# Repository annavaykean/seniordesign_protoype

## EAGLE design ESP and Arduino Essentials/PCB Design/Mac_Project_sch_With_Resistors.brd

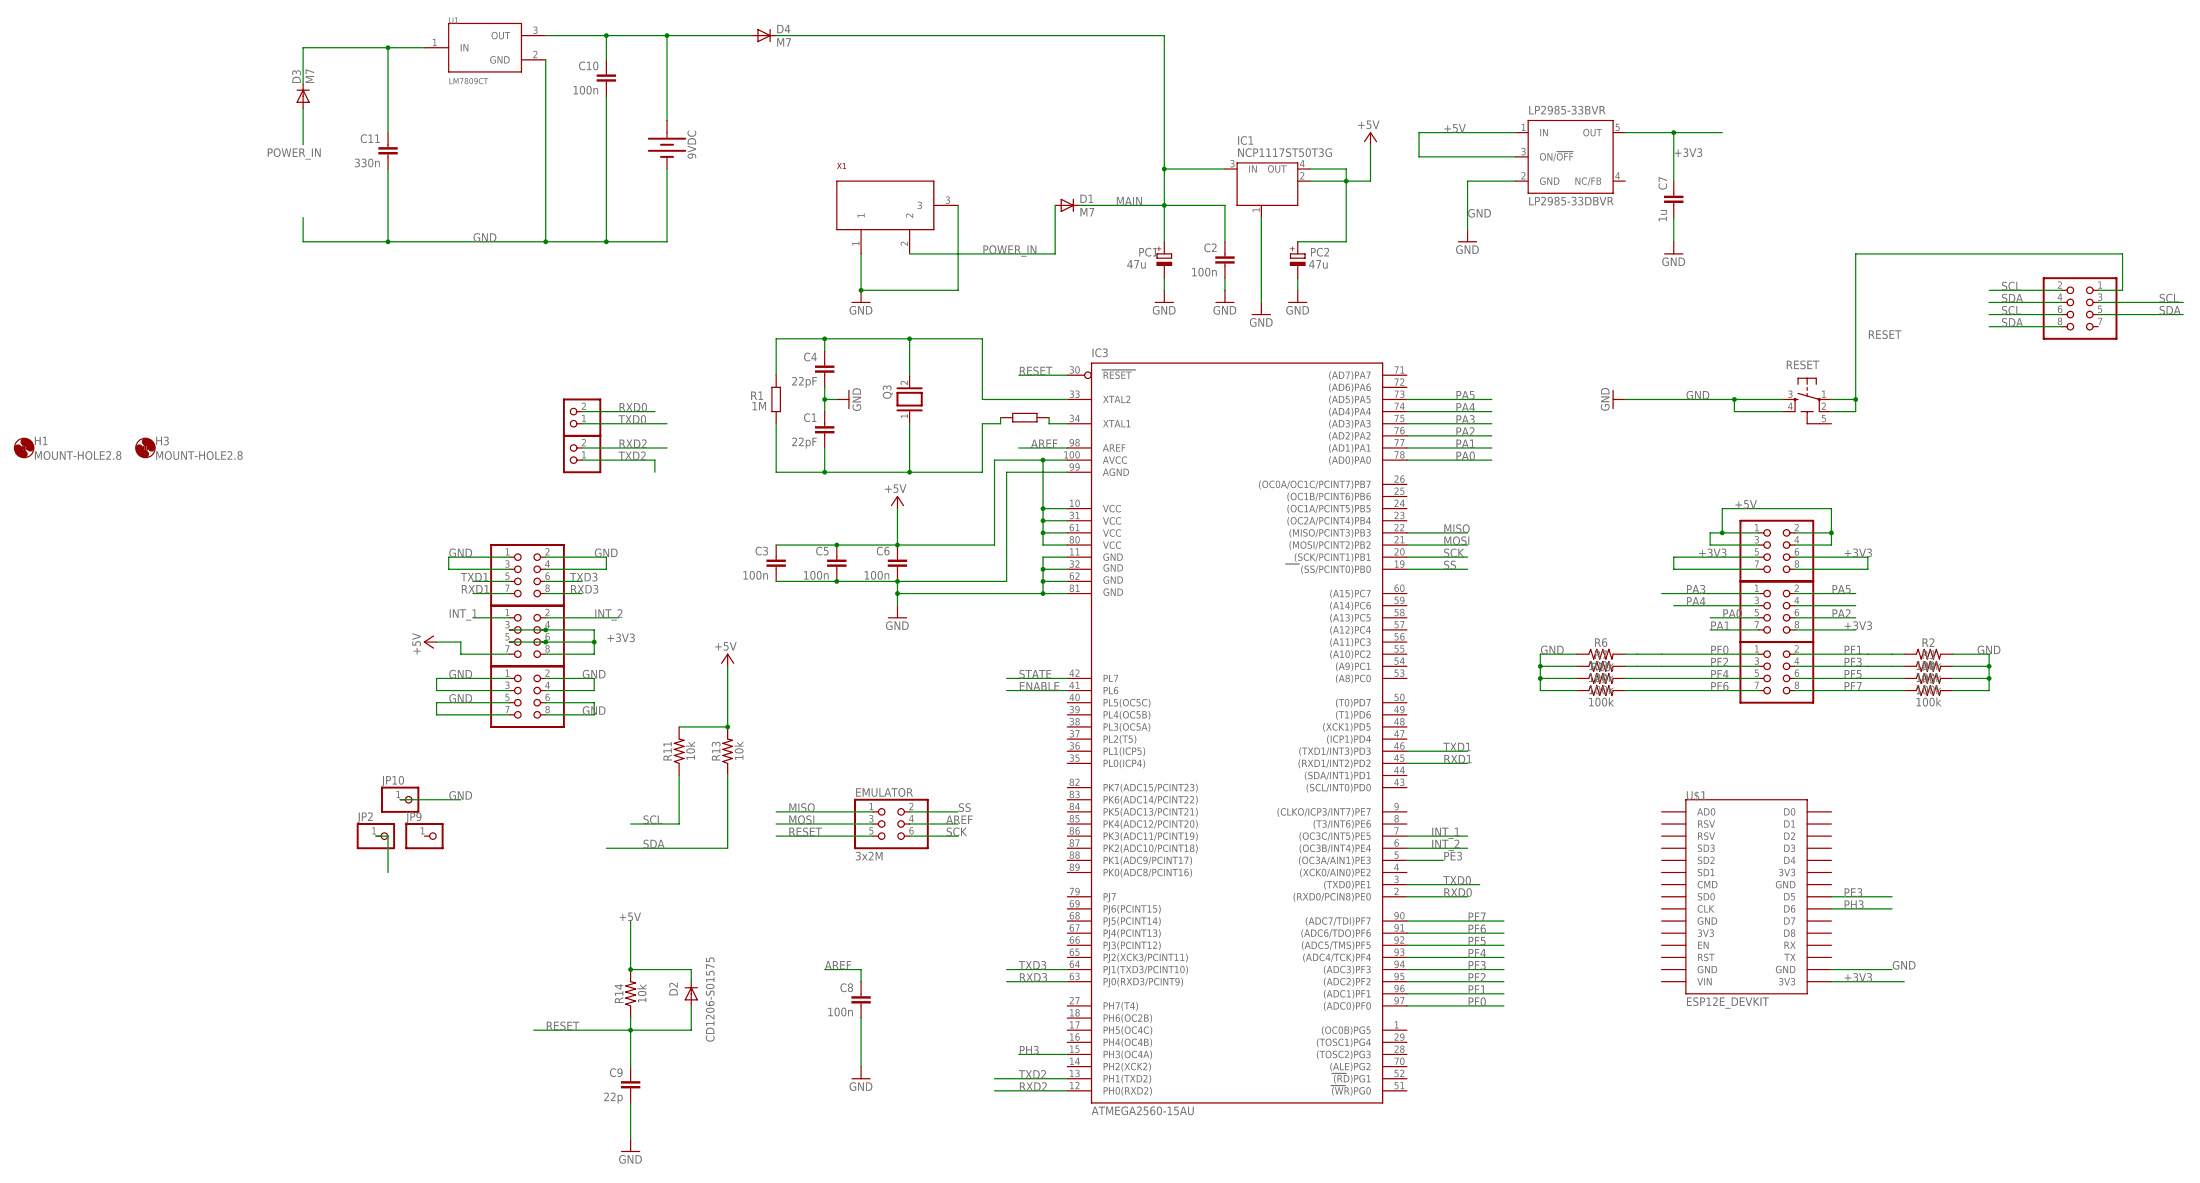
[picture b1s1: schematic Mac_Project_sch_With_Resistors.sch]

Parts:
1X1, 1X2: 1x2; 1X02
9VDC: BATTERY-9V; BATTCON_9V
C1, C4: 22pF; C0603-ROUND
C2, C3, C5, C6, C8, C10: 100n; C0603-ROUND
C7: 1u; C0603-ROUND
C9: 22p; C0603-ROUND
C11: 330n; C0603-ROUND
D1, D3, D4: M7; SMB
D2: CD1206-S01575; MINIMELF
EMULATOR: 3x2M; 2X03
H1, H3: MOUNT-HOLE2.8; 2,8
IC1: NCP1117ST50T3G; SOT223
IC3: ATMEGA2560-15AU; TQFP100
JP1, JP3, JP4, JP5, JP6, JP7, JP8: PINHD-2X4; 2X04
JP2, JP9, JP10: PINHD-1X1; 1X01
LP2985-33BVR: LP2985-33DBVR; SOT23-DBV
PC1, PC2: 47u; PANASONIC_D
Q3: 16MHz; QS
R1: 1M; R0603-ROUND
R2, R3, R4, R5, R6, R7, R9, R10: 100k; 0603
R11, R13, R14: 10k; 0603
R12: 27O; R0603-ROUND
RESET: TS42
U1: LM7809CT; TO254P470X1016X1879-3P
U$1: ESP12E_DEVKIT
X1: POWERSUPPLY_DC21MMX; POWERSUPPLY_DC-21MM

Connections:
5-GND: RESET.5 (5-GND)
+3V3: C7.2, JP3.5, JP3.6, JP3.7, JP3.8, JP4.8, JP7.3, JP7.4, JP7.5, JP7.6, JP7.8, LP2985-33BVR.5 (OUT), U$1.3V3@2 (3V3)
+5V: C3.1, C5.1, C6.1, D2.C, IC1.2 (OUT), IC1.4 (OUT), IC3.10 (VCC), IC3.31 (VCC1), IC3.61 (VCC2), IC3.80 (VCC3), IC3.100 (AVCC), JP3.1, JP3.2, JP3.3, JP3.4, JP7.7, LP2985-33BVR.1 (IN), LP2985-33BVR.3 (ON/!OFF), PC2.+, R11.2, R13.2, R14.2
AREF: C8.1, EMULATOR.4, IC3.98 (AREF)
ENABLE: IC3.41 (PL6)
GND: 9VDC.-, C1.1, C2.2, C3.2, C4.2, C5.2, C6.2, C7.1, C8.2, C9.2, C10.2, C11.2, IC1.1 (GND/ADJ), IC3.11 (GND), IC3.32 (GND1), IC3.62 (GND2), IC3.81 (GND3), IC3.99 (AGND), JP1.1, JP1.2, JP1.3, JP1.4, JP1.5, JP1.6, JP1.7, JP1.8, JP4.4, JP6.1, JP6.2, JP6.3, JP6.4, JP10.1, LP2985-33BVR.2 (GND), PC1.-, PC2.-, R2.2, R3.2, R4.2, R5.2, R6.1, R7.1, R9.1, R10.1, RESET.3, RESET.4, U1.2 (GND), U$1.GND@3 (GND), X1.1, X1.3
INT_1: IC3.7 ((OC3C/INT5)PE5), JP7.1
INT_2: IC3.6 ((OC3B/INT4)PE4), JP7.2
MAIN: C2.1, D1.C, D4.C, IC1.3 (IN), PC1.+
MISO: EMULATOR.1, IC3.22 ((MISO/PCINT3)PB3)
MOSI: EMULATOR.3, IC3.21 ((MOSI/PCINT2)PB2)
unnamed: C4.1, IC3.33 (XTAL2), Q3.2, R1.2
unnamed: C1.2, Q3.1, R1.1, R12.1
unnamed: IC3.34 (XTAL1), R12.2
unnamed: C11.1, D3.C, U1.1 (IN)
unnamed: 9VDC.+, C10.1, D4.A, U1.3 (OUT)
PA0: IC3.78 ((AD0)PA0), JP4.5
PA1: IC3.77 ((AD1)PA1), JP4.7
PA2: IC3.76 ((AD2)PA2), JP4.6
PA3: IC3.75 ((AD3)PA3), JP4.1
PA4: IC3.74 ((AD4)PA4), JP4.3
PA5: IC3.73 ((AD5)PA5), JP4.2
PE3: IC3.5 ((OC3A/AIN1)PE3), U$1.D5
PF0: IC3.97 ((ADC0)PF0), JP8.1, R6.2
PF1: IC3.96 ((ADC1)PF1), JP8.2, R2.1
PF2: IC3.95 ((ADC2)PF2), JP8.3, R7.2
PF3: IC3.94 ((ADC3)PF3), JP8.4, R3.1
PF4: IC3.93 ((ADC4/TCK)PF4), JP8.5, R10.2
PF5: IC3.92 ((ADC5/TMS)PF5), JP8.6, R4.1
PF6: IC3.91 ((ADC6/TDO)PF6), JP8.7, R9.2
PF7: IC3.90 ((ADC7/TDI)PF7), JP8.8, R5.1
PH3: IC3.15 (PH3(OC4A)), U$1.D6
POWER_IN: D1.A, D3.A, X1.2
RESET: C9.1, D2.A, EMULATOR.5, IC3.30 (RESET), JP5.1, R14.1, RESET.1, RESET.2
RXD0: 1X2.2, IC3.2 ((RXD0/PCIN8)PE0)
RXD1: IC3.45 ((RXD1/INT2)PD2), JP6.7
RXD2: 1X1.2, IC3.12 (PH0(RXD2))
RXD3: IC3.63 (PJ0(RXD3/PCINT9)), JP6.8
SCK: EMULATOR.6, IC3.20 ((SCK/PCINT1)PB1)
SCL: JP5.2, JP5.3, JP5.6, R11.1
SDA: JP5.4, JP5.5, JP5.8, R13.1
SS: EMULATOR.2, IC3.19 ((SS/PCINT0)PB0)
STATE: IC3.42 (PL7)
TXD0: 1X2.1, IC3.3 ((TXD0)PE1)
TXD1: IC3.46 ((TXD1/INT3)PD3), JP6.5
TXD2: 1X1.1, IC3.13 (PH1(TXD2))
TXD3: IC3.64 (PJ1(TXD3/PCINT10)), JP6.6

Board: 2 copper layers, 54 parts (0 on the bottom side), 44 nets, no tracks yet.

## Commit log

2019-04-02 initial commit with DB script
2019-04-04 project exists now
2019-04-11 initial flutter project
2019-04-11 100 page doc
2019-04-11 added A's section and fixed A's works cited
2019-04-11 Update 100 page.docx
    my stuff is there and still organizing some
2019-04-11 Moved Schematic to new section
    moved schematic, added description
2019-04-11 Update 100 page.docx
    Heading fixed
2019-04-11 Update 100 page.docx
    partial format fix
2019-04-11 Update 100 page.docx
    go ahead
2019-04-11 Additions and formatting
    added a page from myself and 3.5 pages from mack, reformatted numbering in ch. 4 & 5. TOC taking very long to update
2019-04-12 Update 100 page.docx
    done with my part
2019-04-12 10 pages finished, page count issue
    page counter was incorrect, we are short 8 pages, 6 short from mac. formatting will give us 1/2 page on correcting titel size and spacing.
2019-04-12 added more from mack
    seperately writing more to try and fill mack's gap. go ahead with indexing
2019-04-12 added more texgt and inline citations.
    most of my citations are general so I placed them at the end of the paragraph/section
2019-04-12 citations indexed
2019-04-12 added two pages . we need 1.5
    github is giving me an error in regards to the excel file.
2019-04-12 New
    New document but the same
2019-04-12 renamed file
2019-04-12 fixed stuff
2019-04-12 hit page count
2019-04-13 Updated all headings
    fixed font inconsistencies in headings.
2019-04-18 Create Final Document Research .docx
    new document
2019-04-18 my part is added
2019-04-19 Update Final Document Research .docx
    more from my part
2019-04-19 adding my 5 pgs
2019-04-20 Added pages & labeled tables
    added pages. labeled all tables and figures
2019-04-20 Final doc Research updated
    moved changes over to correct doc
2019-04-20 Update Final Document Research .docx
    updated more bluetooth
2019-04-20 Update Final Document Research .docx
    editing format
2019-04-20 Updates
    Added page. 114 pages, 123 total. need 6. still awaiting 5 from mack
2019-04-20 hit page count
    Added mack's pages.
2019-04-20 Update Final Document Research .docx
    Bluetooth Low Energy
2019-04-20 Update Final Document Research .docx
    more BLE stuff
2019-04-20 Works Cited Fix #1
2019-04-20 works cited to IEEE format Pt.1
2019-04-20 added works cited to main paper
    use the works cited within the body of the paper now!
2019-04-21 Citations Update
    -Added citations to sections missing, moved inline
    -removed 5.1.2.1.2 & 2.2
2019-04-21 added more of Annavay's writing in
2019-04-21 Update Final Document Research .docx
    fixed minor format
2019-04-21 Update fixedWorksCited.docx
    more links
2019-04-21 Update fixedWorksCited.docx
    updated links
2019-04-21 Table updates
    -renumbered tables
2019-04-21 fixed works cited
2019-04-21 Add files via upload
    format fix
2019-04-21 format fixes
2019-04-22 Tables relabeled
    Relabeled tables, adjusted white spaces & orphan headings
    Preliminary proof reading
2019-04-22 Update to 120Final
    -formatting fixes
2019-04-22 updated final and created binded
    binded doc needs review
2019-04-22 small fix
2019-04-22 spacing fix
2019-04-22 undo change
2019-05-08 Super basic page navigation and working on Firebase
2019-05-09 foundation for bluetooth connections
2019-05-13 can scan for bluetooth device, working on display
2019-05-13 kinda displays scanned devices...but causes visual overflow
2019-05-13 prints list of bluetooth devices nearby
2019-05-13 kind of connecting to device
2019-05-14 Thien test this one!
2019-05-15 Update bluetooth_test_screen.dart
    seconds
2019-05-17 uploading notes from first lecture
2019-05-17 notes
2019-05-17 screen to test sending data over bluetooth
2019-05-17 alignment and global connection object for bluetooth
2019-05-19 Important Libaries and Instructions
2019-05-20 updated guides
2019-05-20 with tested code
2019-05-20 bluetooth improvements: display device name & read characteristics
2019-05-20 with code
2019-05-21 fixed bug: duplicate device listings on scan
2019-05-22 kinda-sorta reading characteristics
2019-05-22 minor change for safe testing
2019-05-22 testing the errors
2019-05-23 basic sign in added
2019-05-23 account creation added
2019-05-24 go to dashboard after sign in/up
2019-05-27 changes to alignment
2019-05-27 form validation for sign in
2019-05-27 can write data to database
2019-05-28 Bluetooth Receive Data
2019-05-29 read from firebase database
2019-05-29 bluetooth - sendInt update; database - organize fetched data
2019-05-29 close connection on logout
2019-05-31 more ESP32
2019-05-31 library
2019-05-31 read firebase data and display on UI
2019-05-31 CDR added
2019-05-31 can see database pull
2019-06-03 move folders
2019-06-03 begin work on chart, UI improvements
2019-06-14 added scatter plot
2019-06-16 charts work, adding images
2019-06-18 can recommend pose
    poses recommendations are randomly generated at the moment
    in future will use posture data to tailor recommendations
2019-06-18 added more poses
2019-06-19 more poses; settings screen has toggles
2019-06-20 settings menu alters flags in firebase
2019-06-21 addressed sign out bug
2019-06-21 basic notification working
2019-06-21 notification with noise and vibration
2019-06-21 pin get/set via user preferences
2019-06-24 default data to hold chart shape; trim email to prevent error
2019-06-24 swipe left for settings
2019-06-24 fixed issue of user preferences on sign up
2019-06-25 added long term data
2019-06-27 check if email or pin already used on sign up
2019-06-27 pin verification visuals updated
2019-06-28 phone notification based on firebase flag
2019-06-28 long term data anchor points are now white
2019-07-01 bug fixes
2019-07-02 code 4 demo
2019-07-02 upload
2019-07-02 working serial
2019-07-02 Major bug fix
    cogxy code
2019-07-03 can send pos/neg values
2019-07-03 can receive negative values
2019-07-04 Cogx Cogy sending code
    properly sending cog x & cog y, both negative and positive values. currently under leaning fwd condition
2019-07-04 Sensor to Firebase
    we established the proper serial communication, along along with sending to firebase
2019-07-05 fixed pin bug on sign up
2019-07-05 Create flipped cogxy test.ino
    code for testing flipped x y on recieve and breaking after multiple iterations
2019-07-05 Create cogxcogy_all_conditions.ino
    working transmit for all leaning conditions
2019-07-05 Update cogxcogy_all_conditions.ino
    added additional character to transmit string
2019-07-05 Force Sensor
    the 4 other position is functional
2019-07-05 Update cogxcogy_all_conditions2.ino
    added code to test vibrate modules using leds- good for left & right conditions
2019-07-08 fix signup + new timer (getUp reminder)
2019-07-08 Thien, let's try this
2019-07-09 Create cogxcogy_all_conditions3.ino
    working code for cog x and y no led notifications
2019-07-09 Update cogxcogy_all_conditions3.ino
    added 0 condition
2019-07-09 delay improved garbled data
2019-07-09 working with less errors
2019-07-09 timer code for rudy
2019-07-09 CODE WORKS
    The delay is at 10 seconds and did not give error codes
2019-07-09 fixed chart data load bug
2019-07-09 TURN ON LED/VIBRATOR
2019-07-10 Create cogxcogy_all_conditions4.ino
    added led code to simulate vibrate module. recieves on off trigger
2019-07-10 Create vibtest.ino
    code to run single vibrate module
2019-07-10 Change Firebase Directory to Annavay
2019-07-10 Vibrator Module Included
2019-07-10 Update cogxcogy_all_conditions4.ino
    working vibrate module toggle with bad posture condition.
2019-07-11 Update VIBRATOR_Arduino.ino
    code that sends sensor data to wifi module then to firebase
2019-07-11 My Integrated Code
    some of the code works, so some are just partial
2019-07-12 Full Integration
    Sensor and Vibrator code works and sends to firebase
2019-07-12 Update cogxcogy_all_conditions4.ino
    working code. use file labeled arduino works rev1
2019-07-12 working FSR code & Full duplex code
    FSR fully working in test code
    rev1 is working full duplex. baud cannot exceed 57600 for s.begin
2019-07-12 Clean Code
    Comments and White space are cleaned out on the code
2019-07-12 Update Arduino_works_completely_rev1.ino
    full duplex works correctly
2019-07-12 WiFi Optimized
    wifi does not crash on data read and transmit
2019-07-12 fixing cache issue
2019-07-12 User got up
2019-07-12 Optimize Code
2019-07-14 Update Arduino_works_completely_rev1.ino
    changes to tx3/rx3 works on pcb
2019-07-15 Create Arduino_works_completely_rev2.ino
    updated to include additional sensors and new serial comm pins for pcb
2019-07-15 updated stretch page, added conference paper
2019-07-16 increased anchors on charts
2019-07-16 added intro and overview to conference paper
2019-07-17 rev 3 created
    sensors in final position, cog x & y not updated yet
2019-07-17 Update Arduino_works_completely_rev3.ino
    small test changes
2019-07-17 got 4 pages
2019-07-18 almost 5 pages
2019-07-18 added mack's portion
2019-07-18 proof me
2019-07-18 Organizing format
    Updated biography and formatting
2019-07-18 added A's pic, updated references
2019-07-19 added and formatted references
2019-07-19 fixed bio
2019-07-19 Update ConferencePaper.docx
    new power intro, cleanup
2019-07-19 Update Arduino_works_completely_rev3.ino
    use 51 & 52 for tx/rx (int1 & int2)
2019-07-19 Interrupt
2019-07-20 flush the get up
2019-07-20 Create ATMEGA_fullcode_Rev4.ino
    get up timer works. one vibrate channel works
2019-07-21 Create ATMEGA_fullcode_Rev5.ino
    Code clean up and general formatting, added all sensors to cogx/cogy, removed most print statements
2019-07-21 Create LeaningFlag_Counters_ESP.ino
    simple version of the code for receiving and passing firebase flag. not complete
2019-07-23 final copy of conference paper
2019-07-23 updated anchors and notification settings
2019-07-23 remove extra cdr, fix anchors
2019-07-24 Final Presentation
2019-07-24 removed firePhoneNotif
2019-07-24 updated UI screenshots
2019-07-24 updated ppt
2019-07-24 updating ppt
2019-07-24 created website
2019-07-25 3D Chair Screenshots
2019-07-25 plus 10 to cog
2019-07-25 website update
2019-07-25 Final Code
2019-07-25 updated schematic
2019-07-25 Power Supply PPT
2019-07-25 Update FinalPresentation.pptx
    Updated Cost Table, removed progress chart
2019-07-25 website udpate
2019-07-25 Well timed
2019-07-26 final update of presentation
2019-07-30 Annavay's updates pt1
2019-07-31 Update 120pgFINAL.docx
    Tense changes in first 60pgs, removed figure 5.10- needs to be replaced
2019-07-31 Annavay updates pt2 w/code
2019-07-31 added pubspec
2019-07-31 Communication
    Included Software Serial and library into writing
2019-07-31 3D and Code
    added the 3D chair and code from serial and wireless communication
2019-07-31 formatting
2019-07-31 ESP arrangement
2019-07-31 Implementation section
    added wifi implementation
2019-08-01 Update 120pgFINAL.docx
    added embedded code, wrote section on sensor code. tense updates
2019-08-01 Format Fix
    fixing up spacing and titles
2019-08-01 added firebase stuff
2019-08-01 Wireless Communication
2019-08-01 NodeMCU screenshots
2019-08-01 updated website
2019-08-01 some updates
2019-08-01 typo
2019-08-01 Code Section
    Wrote an intro and explanation of how the code works
2019-08-01 Update 120pgFINAL.docx
    updated hardware intro, tense changes
2019-08-01 Updated WIFi Implementation
2019-08-01 update references
2019-08-02 Final paper with correct margins
2019-08-02 Binded format
2019-08-02 fixed margins
2019-08-02 merge
2019-08-02 updated binded and created new unbinded
2019-08-02 non-binded format
2019-08-02 margins
2019-08-02 update hos
2019-08-02 FINISHED

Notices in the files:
parts and their libraries:
SparkFun-Batteries: Licensing: Creative Commons ShareAlike 4.0 International - https://creativecommons.org/licenses/by-sa/4.0
